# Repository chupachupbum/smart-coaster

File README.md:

# Smart Cup Stand (ESP32-C3 & ESP32)

Firmware, Wokwi hardware simulations, and a custom 2-layer KiCad 10 PCB for an ESP32-C3 / ESP32 hydration tracking coaster. Instead of Time-of-Flight (ToF) distance sensors that only detect whether a bottle was picked up, this system uses a 4-cell Wheatstone bridge load cell and HX711 24-bit ADC to measure beverage mass deltas. It separates real drinks from fidget lifts and refills while driving a 16-pixel WS2812B NeoPixel ring (`LedRing`), UART JSON telemetry, and `ntfy.sh` HTTP push notifications.

## Architecture

The firmware separates hardware-independent hydration state machines from ESP32 peripherals and network services:

- **Core Domain (`lib/coaster_domain/`)**: Pure C++17 state machine (`CupState`, `AlertState`) with zero `<Arduino.h>` dependencies for native host unit testing.
- **Hardware Abstraction Layer (`src/hal/`)**:
  - `WeightSensor`: Non-blocking HX711 driver (`0.42` counts/g default calibration for Wokwi 5 kg load cell).
  - `LedRing`: 16-pixel WS2812B NeoPixel ring driver (`src/hal/led_ring.h` / `src/hal/led_ring.cpp`) on `GPIO 3` (ESP32-C3) / `GPIO 4` (ESP32), rendering intake progress arcs, drink/refill ripples, goal rainbows, stabilization spinners, warm ambient/lifted glows, and reminder/urgent alert patterns. Replaces the active SSD1306 I2C OLED and single PWM status LED (legacy `display_oled.*` and `status_led.*` remain unused in `src/hal/`).
- **Telemetry & CLI (`src/telemetry/`)**: Single-line JSON event/heartbeat emitter and non-blocking UART0 command parser using fixed static buffers (zero heap allocation in steady state).
- **Network Push (`src/net/`)**: Non-blocking Wi-Fi station manager with exponential backoff and bounded FIFO queue (`maxlen=3`, 2000 ms rate limit) dispatching HTTP POST notifications to `ntfy.sh`.
- **Cooperative Scheduler (`src/main.cpp`)**: Rollover-safe multi-rate loop running UART RX polling (continuous), 16-LED ring animations (50 Hz), weight sampling + domain ticks (20 Hz), network dispatch (20 Hz), and telemetry heartbeats (0.2 Hz).

```
├── platformio.ini                   # Build & test config (esp32-c3-devkitm-1, esp32dev, native)
├── diagram.json                     # Default Wokwi schematic (16-pixel WS2812B LED ring + HX711)
├── diagram_led_ring.json            # Wokwi schematic with 16-pixel WS2812 LED ring
├── diagram_round_coaster.json       # Wokwi circular coaster layout (16 radial NeoPixels)
├── wokwi.toml                       # Wokwi firmware binary linkage
├── schematic_led_ring.jpeg          # 16-LED NeoPixel ring wiring diagram (default circuit)
├── schematic_round_coaster.jpeg     # Circular coaster discrete NeoPixel wiring diagram
├── schematic.jpeg                   # Legacy OLED + PWM LED wiring diagram
├── docs/
│   └── app-screens/                 # Companion mobile app UI prototypes (dashboard, alerts, analytics, config)
├── hardware/
│   └── smart_cup_stand_pcb/         # KiCad 10 D-shaped PCB project & JLCPCB manufacturing package
│       ├── smart_cup_stand_pcb.kicad_pro
│       ├── smart_cup_stand_pcb.kicad_sch
│       ├── smart_cup_stand_pcb.kicad_pcb
│       └── manufacturing/           # Gerbers, drill, BOM, CPL, PDFs, DRC/DFM reports, and 3D renders
├── include/
│   ├── pins_config.h                # Multi-target ESP32-C3 & ESP32 pinout + strapping/flash guards
│   ├── config.h                     # Wi-Fi, ntfy.sh, and domain defaults
│   └── secrets.example.h            # Template for local include/secrets.h (gitignored)
├── lib/
│   └── coaster_domain/              # Pure C++ hydration domain state machine
├── src/
│   ├── main.cpp                     # Multi-rate cooperative scheduler
│   ├── hal/                         # HX711 and 16-pixel WS2812B LedRing drivers (plus unused legacy OLED/PWM files)
│   ├── telemetry/                   # UART CLI & single-line JSON telemetry
│   └── net/                         # Wi-Fi manager & ntfy.sh HTTP client
└── test/
    ├── test_coaster_domain/         # Native Unity unit tests (domain logic)
    ├── test_pins_config/            # Native Unity unit tests (ESP32-C3 & ESP32 pin safety invariants)
    └── e2e/                         # 5-tier opaque-box E2E & adversarial test suite
```

## Hydration State Machine & Thresholds

| Parameter | Normal Mode | Demo Mode (`DEMO ON`) | Behavior |
| :--- | :--- | :--- | :--- |
| **Stability Filter** | 1.5 s window, span ≤ 3.0 g | 1.5 s window, span ≤ 3.0 g | Sliding window (`≥ 3` samples); reports arithmetic mean once settled |
| **Empty Auto-Tare** | `±5.0 g` for 5.0 s | `±5.0 g` for 1.0 s | Automatically zeroes load cell drift (`≥ 0.05 g`) while in `EMPTY` |
| **Cup Presence** | `> 30.0 g` (stable) | `> 30.0 g` (stable) | Transitions `EMPTY` → `STABILIZING` → `CUP_PRESENT` and locks baseline |
| **Cup Lift** | `< 20.0 g` | `< 20.0 g` | Transitions `CUP_PRESENT` → `CUP_LIFTED` (hysteresis prevents chatter) |
| **Valid Drink** | `Δ ≤ -15.0 g` | `Δ ≤ -15.0 g` | Logs `baseline - returned` (g ≈ ml) to daily intake, clears alerts, resets timer |
| **Lift Without Drink** | `-15.0 g < Δ < +30.0 g` | `-15.0 g < Δ < +30.0 g` | Updates baseline to track condensation/drift without logging intake or resetting timer |
| **Refill Detection** | `Δ ≥ +30.0 g` | `Δ ≥ +30.0 g` | Updates baseline to new heavier weight; does not log intake or reset timer |
| **Primary Reminder** | 45 minutes | 45 seconds | Enters `ALERT_DUE`, triggers `ALERT_BREATHING` on the 16-LED ring, dispatches push notification |
| **Repeat Reminder** | Every 5 minutes | Every 5 seconds | Enters `ALERT_REPEAT`, triggers `ALERT_URGENT` strobe on the 16-LED ring, re-notifies every interval until a valid drink is logged |
| **Daily Goal** | 2000 ml (default) | 2000 ml (default) | Configurable `100..10000 ml`; triggers `RAINBOW_GOAL` celebration sweep & push notification at 100% |

## Hardware Pinout

The firmware supports two board targets configured in `platformio.ini` and `include/pins_config.h`:

1. **`esp32-c3-devkitm-1` (Default / Wokwi Simulation)**: Avoids ESP32-C3 strapping pins (`GPIO 2`, `GPIO 8`, `GPIO 9`) so external loads cannot hold `GPIO 9` low during reset or conflict with the onboard WS2812 RGB LED on `GPIO 8`.
2. **`esp32dev` (`BOARD_ESP32_CLASSIC` / `ESP32-D0WD-V3`)**: Avoids integrated SPI flash pins (`GPIO 6..11`) and strapping pins (`GPIO 0`, `GPIO 2`, `GPIO 12`, `GPIO 15`).

| Peripheral | Signal | ESP32-C3 Pin (`esp32-c3-devkitm-1`) | Classic ESP32 Pin (`esp32dev`) | Notes |
| :--- | :--- | :--- | :--- | :--- |
| **HX711 Load Cell Amp** | `DT` (DOUT) | `GPIO 6` (J3-9) | `GPIO 18` | 24-bit ADC serial data input |
| **HX711 Load Cell Amp** | `SCK` (PD_SCK) | `GPIO 7` (J3-8) | `GPIO 19` | 24-bit ADC serial clock output |
| **WS2812B 16-LED Ring** | `DIN` | `GPIO 3` (J1-5) | `GPIO 4` | Via 330 Ω series resistor to 16-pixel NeoPixel ring `DIN` |
| **UART0 Console** | `TX` / `RX` | `GPIO 21` / `GPIO 20` | `GPIO 1` / `GPIO 3` | 115200 8N1 interactive CLI & JSON telemetry stream |

### 4-Cell Load Cell Wheatstone Bridge Wiring

Four 3-wire (50 kg) half-bridge load cells form a full Wheatstone bridge into the HX711:
- **Top-Left (`E+`) & Bottom-Right (`E-`)**: Center signal wires connect to `E+` and `E-` excitation pins.
- **Bottom-Left (`A+`) & Top-Right (`A-`)**: Center signal wires connect to `A+` and `A-` differential sense pins.
- **Outer Loop**: Outer red/black half-bridge leads pair with adjacent corners as shown in `schematic.jpeg` so compression on all four feet sums constructively.

### Wokwi Simulation Topologies

The default `diagram.json` uses the 16-pixel WS2812B LED ring topology; an alternate discrete-LED layout is also included:

| Layout | Wokwi Diagram | Schematic | Description |
| :--- | :--- | :--- | :--- |
| **16-LED Ring (Default)** | `diagram.json` / `diagram_led_ring.json` | `schematic_led_ring.jpeg` | `wokwi-led-ring` (16 pixels on `GPIO 3` via 330 Ω resistor) + HX711 |
| **Circular Coaster** | `diagram_round_coaster.json` | `schematic_round_coaster.jpeg` | 16 discrete radially-arranged WS2812 pixels (`led0..led15`) + HX711 |

## Custom PCB & JLCPCB Manufacturing (`hardware/smart_cup_stand_pcb/`)

`hardware/smart_cup_stand_pcb/` holds a 2-layer D-shaped ~50 mm x 40 mm KiCad 10 PCB with 0 ERC violations, 0 DRC violations, and a complete JLCPCB SMT assembly package.

- **Board outline and mounting.** An R = 48 mm curved left USB-C edge fits inside a 100 mm round coaster with a 2 mm enclosure wall. Left M3 mounting holes `H1` and `H4` sit at `x = 108.50 mm`, while right M3 mounting holes `H2` and `H3` sit at `x = 139.50 mm`, `y = 83.50` and `116.50 mm`, clearing `U1`'s antenna courtyard.
- **USB-C power and regulation.** USB-C receptacle `J1`, HRO `TYPE-C-31-M-12`, LCSC `C165948`, protrudes 1.05 mm past the R = 48 mm arc apex so USB-C cable plugs clear the curved shell. Two 5.1 kΩ CC1 and CC2 pulldowns `R1` and `R2` feed an `AMS1117-3.3` LDO `U2`, LCSC `C6186`, and a 10 uF and 100 nF decoupling network `C1..C11`.
- **Orthogonal Wi-Fi edge and perimeter headers.** `ESP32-C3-WROOM-02` module `U1`, LCSC `C2934560`, sits flush with the straight right PCB edge at `x = 150.00 mm` with a 2-layer copper keepout across `x = 144.00..150.00 mm` and `y = 86.00..114.00 mm`. Planar right-angle 2.54 mm headers exit orthogonally into the coaster cavity. North-facing 4-pin Wheatstone bridge header `J2`, XFCN `PZ254R-11-04P`, LCSC `C492412`, carries silkscreen labels `E+`, `E-`, `A-`, `A+` at `x = 126.20, y = 83.85 mm` with 27.8 mm radial wall clearance. South-facing 3-pin WS2812 LED ring header `J3`, XFCN `PZ254R-11-03P`, LCSC `C492411`, carries silkscreen labels `5V`, `DIN`, `GND` at `x = 133.50, y = 116.15 mm` with 31.0 mm radial wall clearance.
- **Analog front-end and buttons.** Top-strip 24-bit ADC `U3`, `HX711` SOIC-16, LCSC `C43656`, pairs with an `SS8550` PNP high-side AVDD transistor `Q1`, LCSC `C2145`, a 20 kΩ and 8.2 kΩ regulator divider `R8` and `R9`, and a 100 Ω differential input filter `R10` and `R11`. Power rails run at `0.50 mm` for `+5V` and `0.40 mm` for `+3V3` and load-cell excitation `LC_E+`. Tactile `TL3342` Reset `SW1` and Boot `SW2` buttons sit along the bottom strip.
- **Manufacturing outputs.** `hardware/smart_cup_stand_pcb/manufacturing/` includes the fabrication and SMT assembly files:
  - `gerbers/` holds 2-layer Gerber X2 files `.gbr` and `.gbrjob` plus the Excellon drill file `smart_cup_stand_pcb.drl`.
  - `bom.csv`, `jlcpcb_bom.csv`, and `cpl.csv` list bill-of-materials entries with LCSC part numbers and pick-and-place centroid coordinates.
  - `schematic.pdf` and `pcb.pdf` provide printable schematic and PCB artwork plots.
  - `erc_report.json`, `drc_report.json`, `dfm_profile_check.json`, `pcb_quality_gate.json`, and `schematic_quality_gate.json` record automated ERC, DRC, and JLCPCB DFM signoff results.
  - `renders/` contains raytraced 3D CAD views `pcb_cad_3d_top.png`, `pcb_cad_3d_bottom.png`, and `pcb_cad_3d_angle.png` alongside photorealistic board renders `pcb_reallife_top.jpg` and `pcb_reallife_angle.jpg`.

## Companion App UI Prototypes (`docs/app-screens/`)

Reference mobile UI screens for the companion hydration app and `ntfy.sh` notification workflow live in `docs/app-screens/`:
- `01_dashboard.png`: Live Smart Coaster hydration progress and cup weight dashboard.
- `02_notifications.png`: Lock-screen push notification prototype (`ntfy.sh` reminder & goal alerts).
- `03_charts_analytics.png`: Daily/weekly hydration intake and sip-size analytics.
- `04_configuration.png`: Coaster Wi-Fi, `ntfy.sh` topic, tare, and reminder interval settings.

## Quick Start

### 1. Configure Wi-Fi & `ntfy.sh` Credentials (Optional)

For Wokwi simulation, the firmware defaults to the open `Wokwi-GUEST` network and public `http://ntfy.sh/smart-cup-stand` topic. For physical hardware deployment, copy the secrets template:

```bash
cp include/secrets.example.h include/secrets.h
```

Edit `include/secrets.h` (which is gitignored and automatically included by `include/config.h` via `__has_include("secrets.h")`):

```cpp
#define WIFI_SSID           "your-wifi-ssid"
#define WIFI_PASSWORD       "your-wifi-password"
#define NTFY_SERVER_URL     "http://ntfy.sh"
#define NTFY_DEFAULT_TOPIC  "smart-coaster-your-private-topic"
```

### 2. Build Firmware with PlatformIO

```bash
# Compile ESP32-C3 firmware (.pio/build/esp32-c3-devkitm-1/firmware.bin)
pio run -e esp32-c3-devkitm-1

# Or compile Classic ESP32 firmware (.pio/build/esp32dev/firmware.bin)
pio run -e esp32dev

# Flash to physical board and open serial monitor
pio run -e esp32-c3-devkitm-1 -t upload -t monitor
```

### 3. Run in Wokwi Simulator

1. Install the **Wokwi Simulator** extension for VS Code (or Wokwi CLI).
2. Build the firmware first (`pio run -e esp32-c3-devkitm-1`).
3. Open `diagram.json` (or `diagram_round_coaster.json`) and start the simulation. Use the HX711 weight slider to simulate placing a cup (`> 30 g`), lifting (`< 20 g`), drinking (`≥ 15 g` lighter), and refilling (`≥ 30 g` heavier).

## UART CLI & Telemetry Protocol

Connect to UART0 at `115200` baud (`LF`, `CR`, or `CRLF` line endings).

### Interactive Commands

| Command | Description | Example Response |
| :--- | :--- | :--- |
| `DEMO ON` | Enable 60x time acceleration (45s reminder, 5s repeat, 1s tare) | `{"status":"OK","command":"DEMO ON","demo_mode":true}` |
| `DEMO OFF` | Restore normal production timers (45m reminder, 5m repeat, 5s tare) | `{"status":"OK","command":"DEMO OFF","demo_mode":false}` |
| `TARE` | Zero the scale at the current raw weight and clear baseline | `{"status":"OK","command":"TARE","tare_offset_g":12.4}` |
| `RESET` | Reset daily consumed intake, drink count, and active alerts | `{"status":"OK","command":"RESET","consumed_ml":0.0}` |
| `GOAL <ml>` | Set daily hydration target (`100` to `10000` ml) | `{"status":"OK","command":"GOAL","daily_goal_ml":2500.0,"progress_pct":10.0}` |
| `STATUS` | Emit full snapshot of current coaster state and metrics | `{"status":"OK","command":"STATUS","cup_state":"CUP_PRESENT",...}` |

### Single-Line JSON Telemetry Stream

Telemetry packets are emitted on every domain event (`CUP_PLACED`, `CUP_LIFTED`, `DRINK_LOGGED`, `LIFT_NO_DRINK`, `REFILL_DETECTED`, `REMINDER_ALERT`, `REPEAT_ALERT`, `AUTO_TARE_APPLIED`, `GOAL_REACHED`) and periodically every `5000 ms` (`HEARTBEAT`):

```json
{"event":"DRINK_LOGGED","time_ms":42500,"net_weight_g":280.0,"cup_state":"CUP_PRESENT","alert_state":"COUNTING","is_stable":true,"consumed_ml":120.0,"daily_goal_ml":2000.0,"intake_pct":6.0,"remind_countdown_s":2700,"demo_mode":false,"state":"CUP_PRESENT","weight_g":280.0,"goal_ml":2000.0,"countdown_s":2700,"stable":true,"demo":false}
```

## Testing

The repository includes native C++ unit tests and a 5-tier opaque-box End-to-End (E2E) verification suite.

```bash
# 1. Run C++ native unit tests (domain state machine + pin safety invariants)
pio test -e native

# 2. Run the full 5-tier Python E2E test suite (172 tests across Tiers 1-5)
python3 test/e2e/run_e2e_tests.py

# Or run via pytest
python3 -m pytest test/e2e -v
```

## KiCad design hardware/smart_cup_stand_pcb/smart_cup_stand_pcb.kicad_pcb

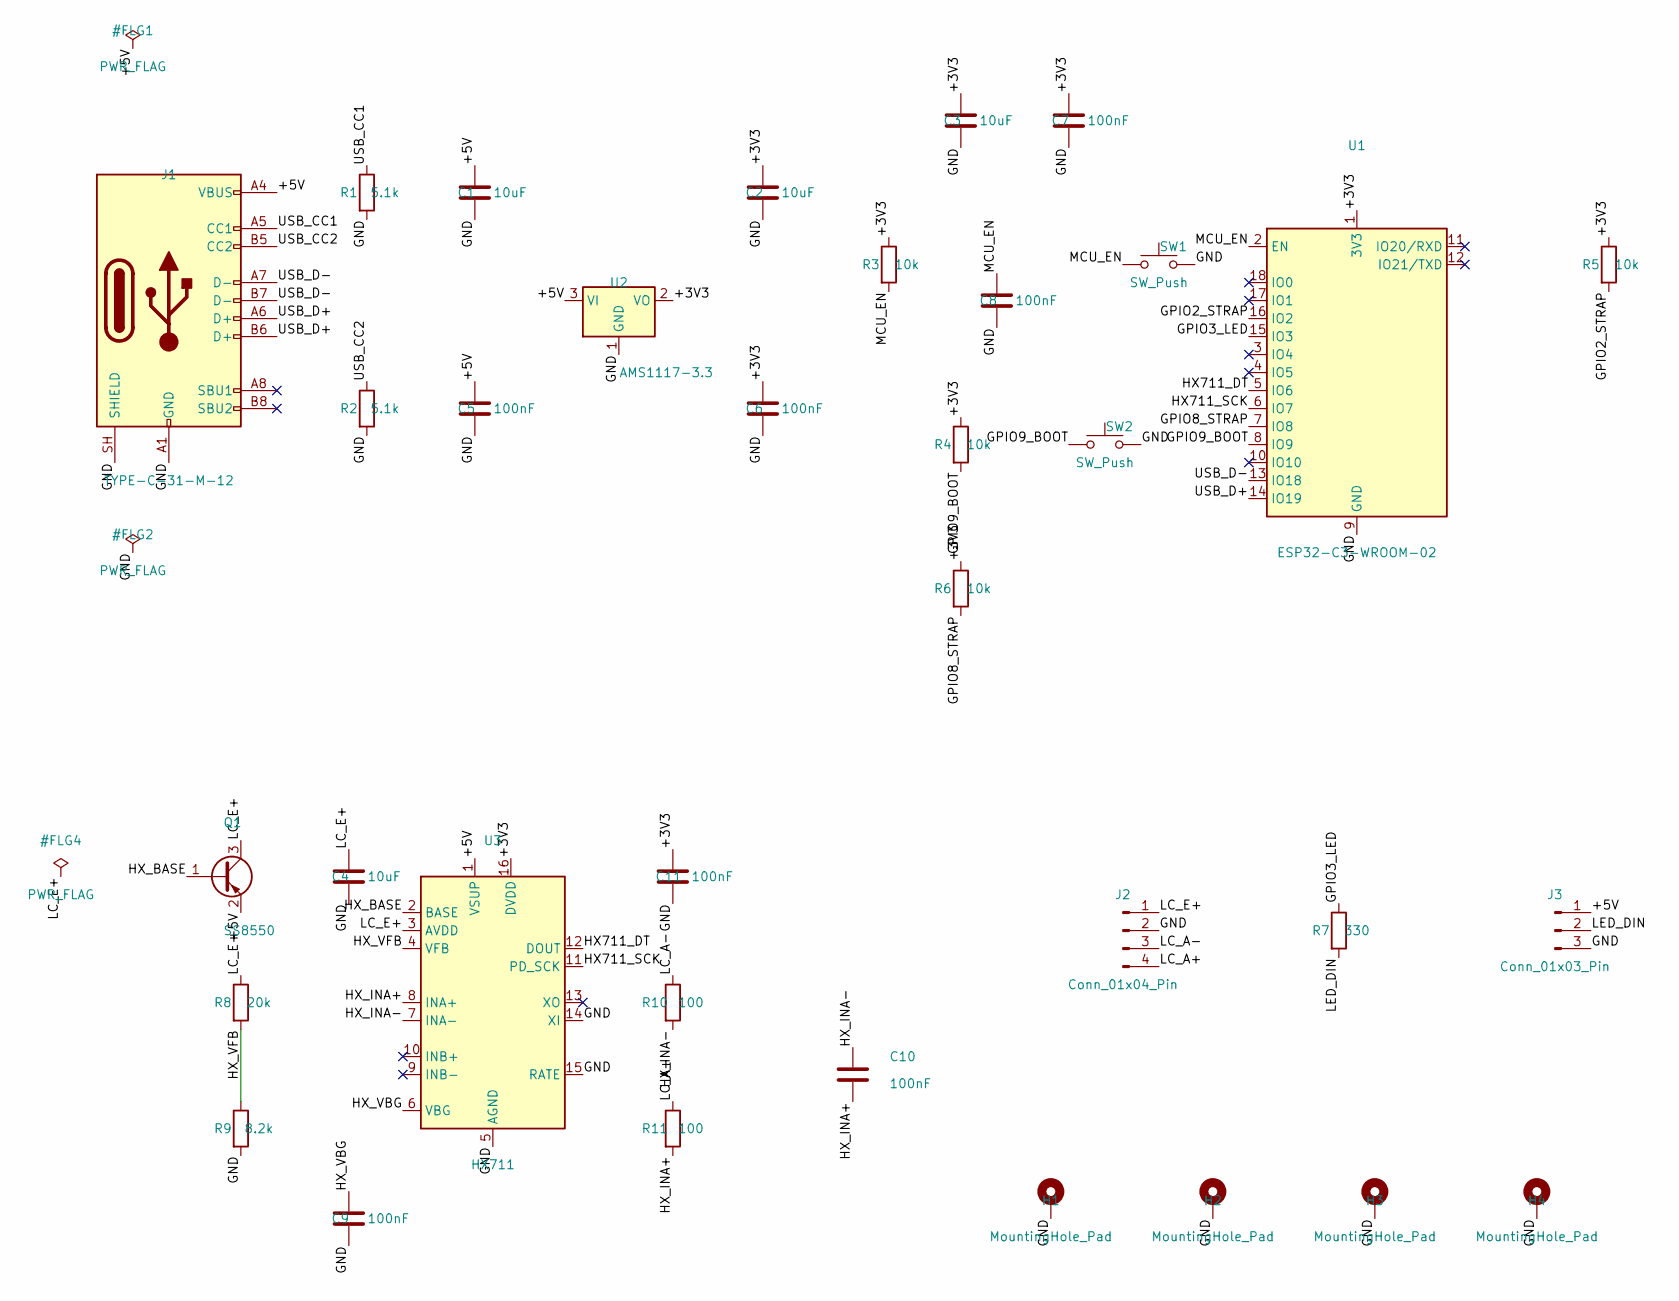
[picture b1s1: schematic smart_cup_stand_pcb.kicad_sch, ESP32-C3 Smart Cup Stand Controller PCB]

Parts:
C1, C2, C3, C4: 10uF; C_0805_2012Metric; LCSC C15850
C5, C6, C7, C8, C9, C10, C11: 100nF; C_0603_1608Metric; LCSC C14663
H1, H2, H3, H4: MountingHole_Pad; MountingHole_3.2mm_M3_Pad
J1: TYPE-C-31-M-12; USB_C_Receptacle_HRO_TYPE-C-31-M-12; LCSC C165948
J2: Conn_01x04_Pin; PinHeader_1x04_P2.54mm_Horizontal; LCSC C492412
J3: Conn_01x03_Pin; PinHeader_1x03_P2.54mm_Horizontal; LCSC C492411
Q1: SS8550; SOT-23; LCSC C2145
R1, R2: 5.1k; R_0603_1608Metric; LCSC C23186
R3, R4, R5, R6: 10k; R_0603_1608Metric; LCSC C25804
R7: 330; R_0603_1608Metric; LCSC C23138
R8: 20k; R_0603_1608Metric; LCSC C4184
R9: 8.2k; R_0603_1608Metric; LCSC C23254
R10, R11: 100; R_0603_1608Metric; LCSC C22775
SW1, SW2: SW_Push; SW_SPST_TL3342; LCSC C318884
U1: ESP32-C3-WROOM-02; LCSC C2934560
U2: AMS1117-3.3; SOT-223-3_TabPin2; LCSC C6186
U3: HX711; SOIC-16_3.9x9.9mm_P1.27mm; LCSC C43656

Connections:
+3V3: C2.1, C3.1, C6.1, C7.1, C11.1, R3.1, R4.1, R5.1, R6.1, U1.1 (3V3), U2.2 (VO), U3.16 (DVDD)
+5V: C1.1, C5.1, J1.A4 (VBUS), J1.A9 (VBUS), J1.B4 (VBUS), J1.B9 (VBUS), J3.1, Q1.2 (E), U2.3 (VI), U3.1 (VSUP)
GND: C1.2, C2.2, C3.2, C4.2, C5.2, C6.2, C7.2, C8.2, C9.2, C11.2, H1.1, H2.1, H3.1, H4.1, J1.A1 (GND), J1.A12 (GND), J1.B1 (GND), J1.B12 (GND), J1.SH (SHIELD), J2.2, J3.3, R1.2, R2.2, R9.2, SW1.2, SW2.2, U1.9 (GND), U1.19 (GND), U2.1 (GND), U3.5 (AGND), U3.14 (XI), U3.15 (RATE)
GPIO2_STRAP: R5.2, U1.16 (IO2)
GPIO3_LED: R7.1, U1.15 (IO3)
GPIO8_STRAP: R6.2, U1.7 (IO8)
GPIO9_BOOT: R4.2, SW2.1, U1.8 (IO9)
HX711_DT: U1.5 (IO6), U3.12 (DOUT)
HX711_SCK: U1.6 (IO7), U3.11 (PD_SCK)
HX_BASE: Q1.1 (B), U3.2 (BASE)
HX_INA+: C10.2, R11.2, U3.8 (INA+)
HX_INA-: C10.1, R10.2, U3.7 (INA-)
HX_VBG: C9.1, U3.6 (VBG)
HX_VFB: R8.2, R9.1, U3.4 (VFB)
LC_A+: J2.4, R11.1
LC_A-: J2.3, R10.1
LC_E+: C4.1, J2.1, Q1.3 (C), R8.1, U3.3 (AVDD)
LED_DIN: J3.2, R7.2
MCU_EN: C8.1, R3.2, SW1.1, U1.2 (EN)
USB_CC1: J1.A5 (CC1), R1.1
USB_CC2: J1.B5 (CC2), R2.1
USB_D+: J1.A6 (D+), J1.B6 (D+), U1.14 (IO19)
USB_D-: J1.A7 (D-), J1.B7 (D-), U1.13 (IO18)

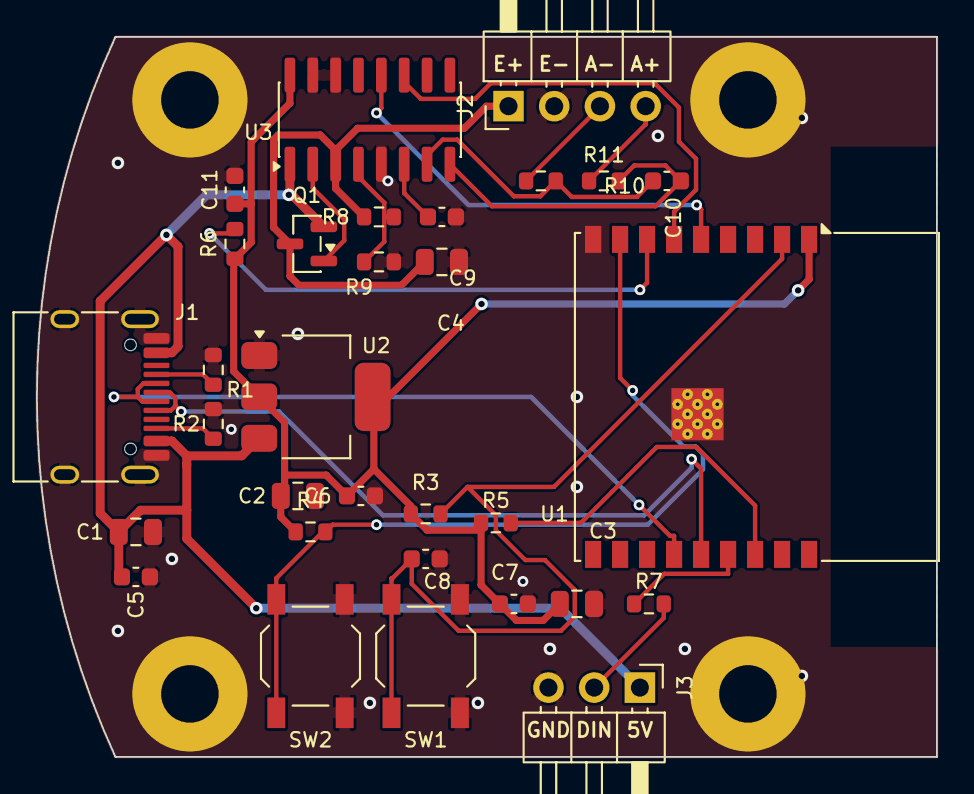
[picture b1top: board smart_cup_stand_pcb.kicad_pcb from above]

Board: 2 copper layers, 50.0 x 40.0 mm, 35 parts (0 on the bottom side), 23 nets.

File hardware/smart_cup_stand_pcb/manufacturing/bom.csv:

Reference,Value,Footprint,Quantity,LCSC Part Number
"C1, C2, C3, C4",10uF,Capacitor_SMD:C_0805_2012Metric,4,C15850
"C5, C6, C7, C8, C9, C10, C11",100nF,Capacitor_SMD:C_0603_1608Metric,7,C14663
J1,TYPE-C-31-M-12,Connector_USB:USB_C_Receptacle_HRO_TYPE-C-31-M-12,1,C165948
J2,Conn_01x04_Pin,Connector_PinHeader_2.54mm:PinHeader_1x04_P2.54mm_Horizontal,1,C492412
J3,Conn_01x03_Pin,Connector_PinHeader_2.54mm:PinHeader_1x03_P2.54mm_Horizontal,1,C492411
Q1,SS8550,Package_TO_SOT_SMD:SOT-23,1,C2145
"R1, R2",5.1k,Resistor_SMD:R_0603_1608Metric,2,C23186
"R3, R4, R5, R6",10k,Resistor_SMD:R_0603_1608Metric,4,C25804
R7,330,Resistor_SMD:R_0603_1608Metric,1,C23138
R8,20k,Resistor_SMD:R_0603_1608Metric,1,C4184
R9,8.2k,Resistor_SMD:R_0603_1608Metric,1,C23254
"R10, R11",100,Resistor_SMD:R_0603_1608Metric,2,C22775
"SW1, SW2",SW_Push,Button_Switch_SMD:SW_SPST_TL3342,2,C318884
U1,ESP32-C3-WROOM-02,RF_Module:ESP32-C3-WROOM-02,1,C2934560
U2,AMS1117-3.3,Package_TO_SOT_SMD:SOT-223-3_TabPin2,1,C6186
U3,HX711,Package_SO:SOIC-16_3.9x9.9mm_P1.27mm,1,C43656
